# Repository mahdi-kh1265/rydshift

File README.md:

# rydshift
A programmable geometric-phase electro-optic frequency shifter and chirp generator for Rydberg excitation.

# Rotating Electro-Optic / Geometric-Phase Frequency Shifter Modeling Handoff

This package is a Jupyter-first modeling handoff for the bulk z-cut LiNbO3 rotating-electro-optic project.

The goal is to get to an "80% of Ansys" level of design confidence without using a full commercial EM/RF simulator. The planned model stack is:

1. **Electro-optic tensor model** for z-cut LiNbO3 propagation along the optic axis.
2. **2D/2.5D electrostatic model** of the four-electrode geometry to compute field-per-volt, field uniformity, and the capacitance matrix.
3. **RF load/current model** for the EO electrode capacitance, including high-current limits at 6-100+ MHz.
4. **LDMOS/GaN RF PA output-network model** where the EO capacitance is part of the final load/match rather than a random external load.
5. **Quadrature-error and optical-efficiency model** to connect amplitude/phase errors to rotating eigenaxis errors, spurs, and geometric-phase frequency-shift performance.
6. **Predistortion / closed-loop calibration scaffold**, eventually using measured S-parameters and electrode-voltage pickups to generate corrected drive waveforms.

## Suggested workflow

Start here:

```bash
python -m venv .venv
source .venv/bin/activate  # Windows: .venv\Scripts\activate
pip install -r requirements.txt
jupyter lab
```

Then work through notebooks in order:

```text
00_project_constants.ipynb
01_eo_retardance_and_vpi.ipynb
02_electrostatic_field_and_capacitance.ipynb
03_rf_load_current_budget.ipynb
04_ldmos_output_network_screening.ipynb
05_quadrature_chirp_and_dpd_scaffold.ipynb
```

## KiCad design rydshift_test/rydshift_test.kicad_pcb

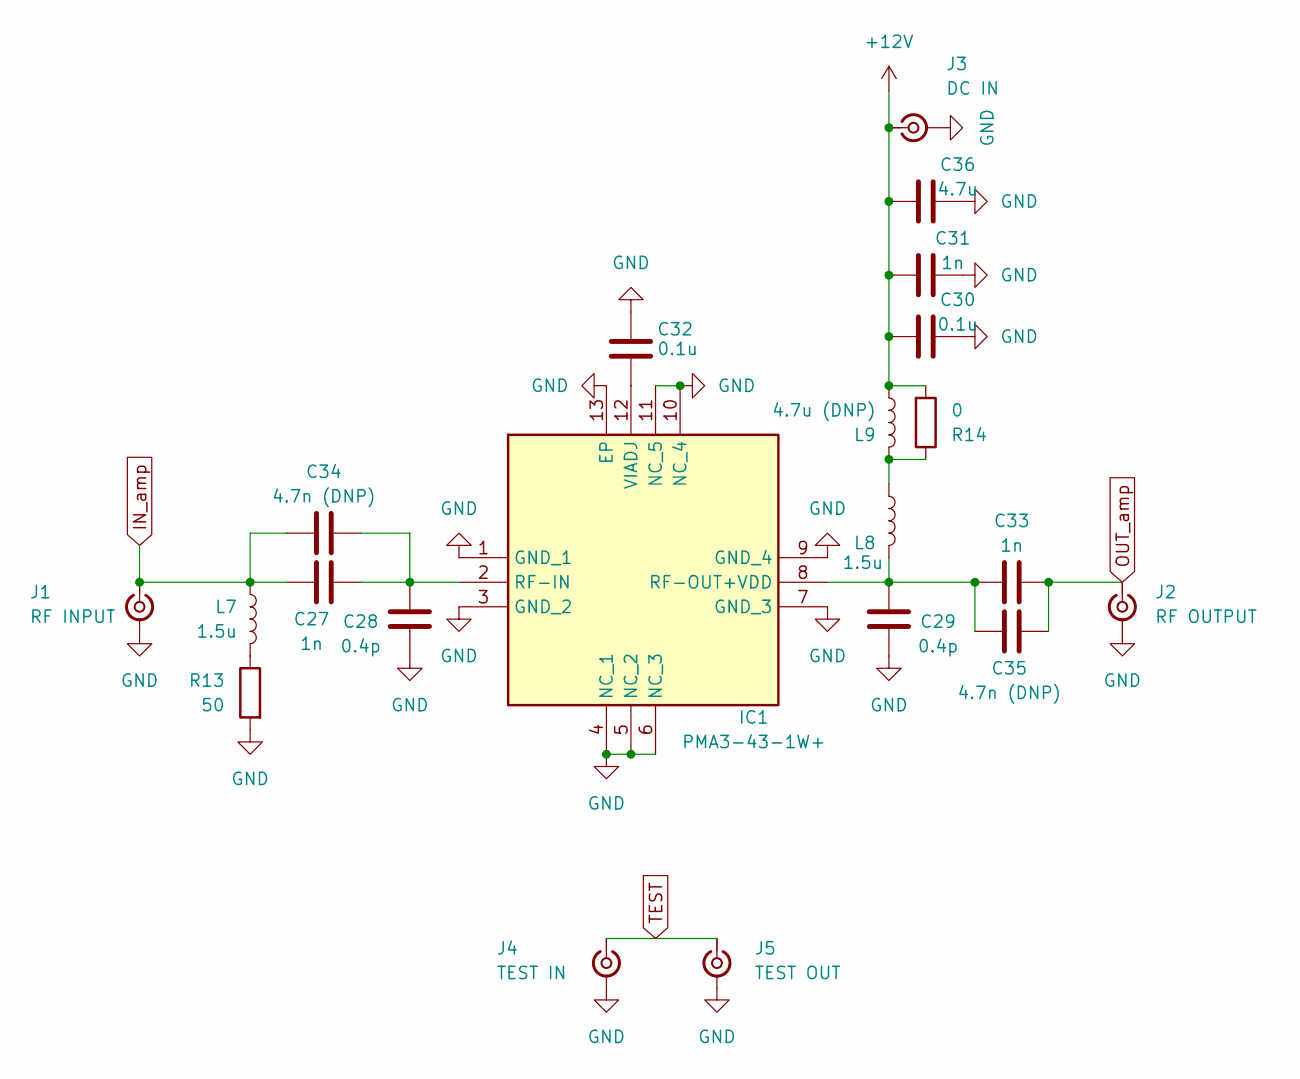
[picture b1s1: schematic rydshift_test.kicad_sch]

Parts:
C27, C33: 1n; C_0805_2012Metric
C28, C29: 0.4p; C_0805_2012Metric
C30: 0.1u; C_0603_1608Metric
C31: 1n; C_0402_1005Metric
C32: 0.1u; C_0402_1005Metric
C34, C35: 4.7n (DNP); C_0805_2012Metric
C36: 4.7u; C_0603_1608Metric
IC1: PMA3-43-1W+; QFN51P300X300X89-13N; Manufacturer_Part_Number PMA3-43-1W+
J1: RF INPUT; SMA_Samtec_SMA-J-P-H-ST-EM1_EdgeMount
J2: RF OUTPUT; SMA_Samtec_SMA-J-P-H-ST-EM1_EdgeMount
J3: DC IN; SMA_Samtec_SMA-J-P-H-ST-EM1_EdgeMount
J4: TEST IN; SMA_Samtec_SMA-J-P-H-ST-EM1_EdgeMount
J5: TEST OUT; SMA_Samtec_SMA-J-P-H-ST-EM1_EdgeMount
L7, L8: 1.5u; L_0805_2012Metric
L9: 4.7u (DNP); L_0805_2012Metric
R13: 50; R_0402_1005Metric
R14: 0; R_0402_1005Metric

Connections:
+12V: C30.1, C31.1, C36.1, J3.1 (In), L9.1, R14.2
GND: C28.1, C29.1, C30.2, C31.2, C32.1, C36.2, IC1.1 (GND_1), IC1.3 (GND_2), IC1.4 (NC_1), IC1.5 (NC_2), IC1.6 (NC_3), IC1.7 (GND_3), IC1.9 (GND_4), IC1.10 (NC_4), IC1.11 (NC_5), IC1.13 (EP), J1.2 (Ext), J2.2 (Ext), J3.2 (Ext), J4.2 (Ext), J5.2 (Ext), R13.2
IN_amp: C27.1, C34.1, J1.1 (In), L7.2
unnamed: C27.2, C28.2, C34.2, IC1.2 (RF-IN)
unnamed: C29.2, C33.1, C35.1, IC1.8 (RF-OUT+VDD), L8.2
unnamed: C32.2, IC1.12 (VIADJ)
unnamed: L7.1, R13.1
unnamed: L8.1, L9.2, R14.1
OUT_amp: C33.2, C35.2, J2.1 (In)
TEST: J4.1 (In), J5.1 (In)

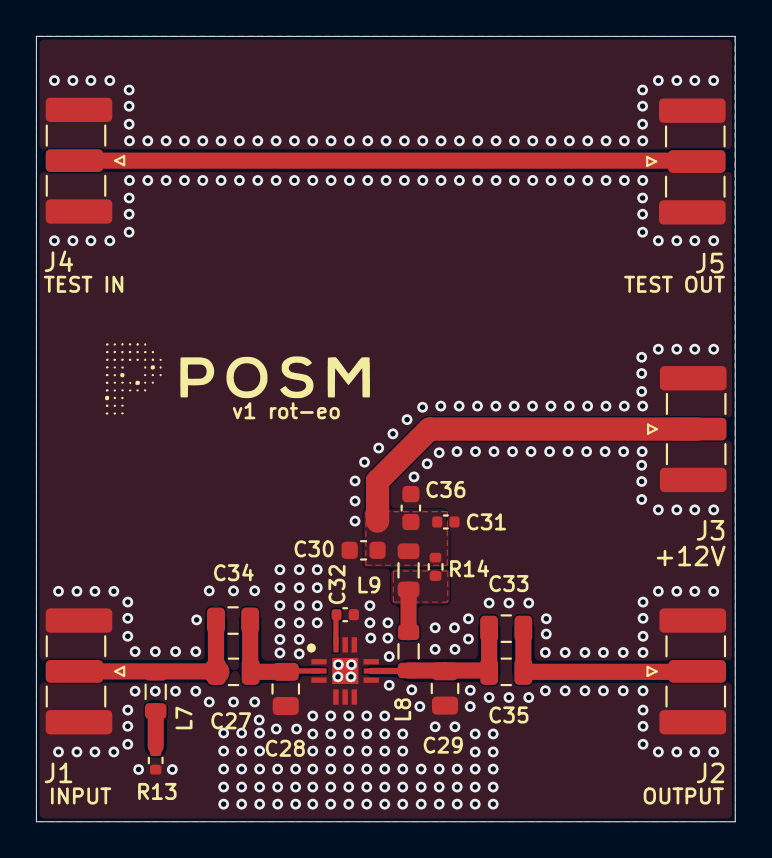
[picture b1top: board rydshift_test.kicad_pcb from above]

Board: 2 copper layers, 38.8 x 43.6 mm, 21 parts (0 on the bottom side), 10 nets.
